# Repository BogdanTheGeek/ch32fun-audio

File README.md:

# Audio Playback on a CH32V00X
Example code for playing audio on a CH32V006 using PWM and DMA.

## Hardware
Small speaker connected to PC3 though a large capacitor(in series), at least 10uF.

The example PCB is designed for experimentation, therefore it also includes USB, SPI-FLASH and a can use the internal OPAMP as a second order low-pass filter. All of these features are optional.

## Getting Started
1. Get everything:
```sh
git clone --recurse-submodules
```
2. Build tools:
```sh
make tools
```
3. Convert audio file to code:
```sh
./tools/wav2code beep-boop.wav > samples.h
```
4. Build and flash:
```sh
make
```
5. Run and interract with the program:
```sh
make monitor
```

> [!WARNING]
> Make sure the audio file is encoded as 16-bit signed PCM, mono, and 32kHz sample rate(this can be adjusted).

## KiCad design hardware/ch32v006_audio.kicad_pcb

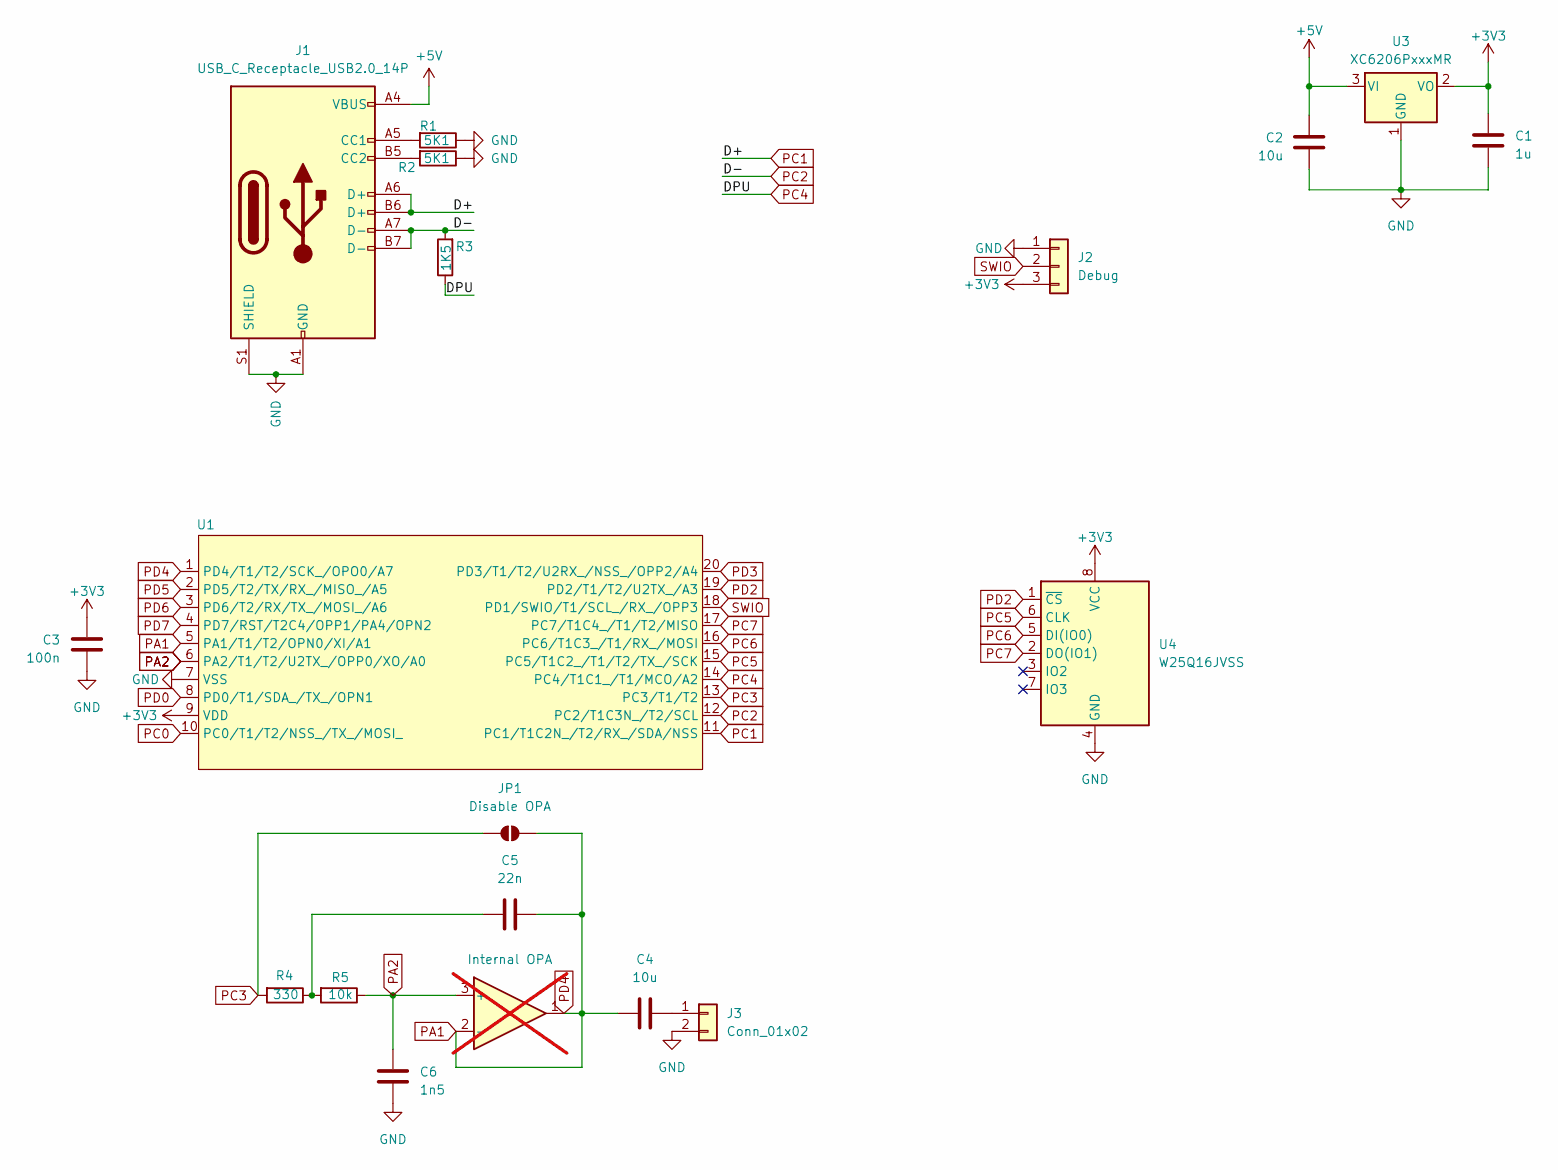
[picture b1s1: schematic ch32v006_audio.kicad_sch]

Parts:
C1: 1u; C_0805_2012Metric_Pad1.18x1.45mm_HandSolder
C2, C4: 10u; C_0805_2012Metric_Pad1.18x1.45mm_HandSolder
C3: 100n; C_0603_1608Metric
C5: 22n; C_0603_1608Metric
C6: 1n5; C_0603_1608Metric
J1: USB_C_Receptacle_USB2.0_14P; USB_C_PADDLE
J2: Debug; PinSocket_1x03_P2.54mm_Vertical
J3: Conn_01x02; PinHeader_1x02_P2.54mm_Vertical
JP1: Disable OPA; SolderJumper-2_P1.3mm_Open_TrianglePad1.0x1.5mm
R1, R2: 5K1; R_0603_1608Metric
R3: 1K5; R_0603_1608Metric
R4: 330; R_1206_3216Metric
R5: 10k; R_0603_1608Metric
U1: TSSOP-20_4.4x6.5mm_P0.65mm
U2: Internal OPA; not fitted
U3: XC6206PxxxMR; SOT-23-3
U4: W25Q16JVSS; SOIC-8_5.23x5.23mm_P1.27mm

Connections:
+3V3: C1.1, C3.1, J2.3, U1.9 (VDD), U3.2 (VO), U4.8 (VCC)
+5V: C2.1, J1.A4 (VBUS), J1.A9 (VBUS), J1.B4 (VBUS), J1.B9 (VBUS), U3.3 (VI)
GND: C1.2, C2.2, C3.2, C6.2, J1.A1 (GND), J1.A12 (GND), J1.B1 (GND), J1.B12 (GND), J1.S1 (SHIELD), J2.1, J3.2, R1.1, R2.1, U1.7 (VSS), U3.1 (GND), U4.4 (GND)
unnamed: C5.1, R4.1, R5.2
unnamed: J1.A5 (CC1), R1.2
unnamed: J1.B5 (CC2), R2.2
unnamed: C4.2, J3.1
PA1: C4.1, C5.2, JP1.2 (B), U1.1 (PD4/T1/T2/SCK_/OPO0/A7), U1.5 (PA1/T1/T2/OPN0/XI/A1), U2.1, U2.2 (-)
PA2: C6.1, R5.1, U1.6 (PA2/T1/T2/U2TX_/OPP0/XO/A0), U2.3 (+)
PC0: U1.10 (PC0/T1/T2/NSS_/TX_/MOSI_)
PC1: J1.A6 (D+), J1.B6 (D+), U1.11 (PC1/T1C2N_/T2/RX_/SDA/NSS)
PC2: J1.A7 (D-), J1.B7 (D-), R3.2, U1.12 (PC2/T1C3N_/T2/SCL)
PC3: JP1.1 (A), R4.2, U1.13 (PC3/T1/T2)
PC4: R3.1, U1.14 (PC4/T1C1_/T1/MCO/A2)
PC5: U1.15 (PC5/T1C2_/T1/T2/TX_/SCK), U4.6 (CLK)
PC6: U1.16 (PC6/T1C3_/T1/RX_/MOSI), U4.5 (DI(IO0))
PC7: U1.17 (PC7/T1C4_/T1/T2/MISO), U4.2 (DO(IO1))
PD0: U1.8 (PD0/T1/SDA_/TX_/OPN1)
PD2: U1.19 (PD2/T1/T2/U2TX_/A3), U4.1 (~CS)
PD3: U1.20 (PD3/T1/T2/U2RX_/NSS_/OPP2/A4)
PD5: U1.2 (PD5/T2/TX/RX_/MISO_/A5)
PD6: U1.3 (PD6/T2/RX/TX_/MOSI_/A6)
PD7: U1.4 (PD7/RST/T2C4/OPP1/PA4/OPN2)
SWIO: J2.2, U1.18 (PD1/SWIO/T1/SCL_/RX_/OPP3)

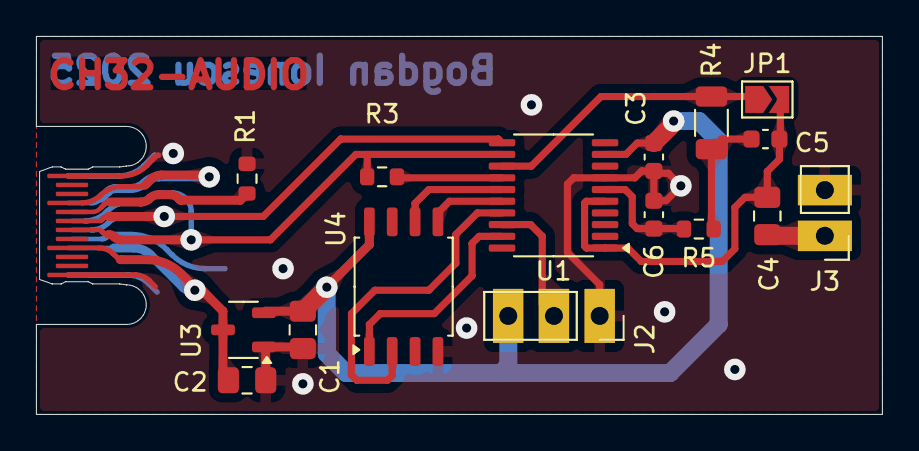
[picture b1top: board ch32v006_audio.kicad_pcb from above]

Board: 2 copper layers, 47.0 x 21.0 mm, 18 parts (1 on the bottom side), 18 nets.

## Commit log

2025-06-28 add submodule
2025-06-28 Update README.md
    add pcb photo
2025-06-28 complementary output boosts power
